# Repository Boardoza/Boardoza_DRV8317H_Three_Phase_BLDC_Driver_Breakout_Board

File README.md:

# Boardoza DRV8317H Three-Phase BLDC Motor Driver Breakout Board

The **Boardoza DRV8317H Breakout Board** is a high-performance, integrated **three-phase BLDC motor driver** designed for compact and efficient motor control applications. Based on the **Texas Instruments DRV8317H**, this device integrates three half-bridges with low R<sub>DS(ON)</sub> MOSFETs, programmable current sensing, and advanced protection mechanisms into a single solution.

Supporting supply voltages up to **24V (absolute maximum)** and delivering up to **5A peak output current**, the DRV8317H is ideal for robotics, steward and gimbal systems, drones, industrial automation, pumps, and smart motorized systems. With flexible control options such as **6x PWM mode and 3x PWM mode**, this board allows both simple and advanced motor control implementations.

## [Click here to purchase!](https://www.ozdisan.com/ureticiler/boardoza)

| Front Side | Back Side |
|:---:|:---:|
|  |  |

---

## Key Features

- **Integrated Three-Phase Driver:** Drives BLDC and PMSM motors with a compact all-in-one solution.
- **Up to 5A Peak Output Current:** Suitable for medium-power motor applications.
- **Flexible Control Options:** Supports **6x PWM** and **3x PWM**.
- **High PWM Frequency Support:** Operates with PWM frequencies up to **200 kHz**.
- **Integrated Current Sensing:** No external shunt resistor required.
- **Programmable Slew Rate:** Helps reduce EMI and optimize switching performance.
- **Comprehensive Protection Features:** Includes UVLO, OVP, CPUV, OCP, OTW, and OTS protections.
- **Shoot-Through Protection:** Integrated hardware-level safety for reliable operation.

---

## Technical Specifications

**Model:** DRV8317H  
**Manufacturer:** Boardoza  
**Manufacturer IC:** Texas Instruments  
**Driver Type:** Integrated 3-Phase Gate Driver with MOSFETs  
**Functions:** Three-Phase PWM BLDC Motor Driver  
**Input Voltage (VM):** 4.5V – 20V (24V Absolute Maximum)  
**Peak Output Current:** 5A (per phase, peak)  
**Control Interfaces:** 6x PWM / 3x PWM    
**Maximum PWM Frequency:** 200 kHz  
**RDS(ON) (HS + LS):** 130 mΩ (typical at 25°C)  
**Current Sensing:** Integrated (Programmable Gain)  
**Protection Features:**  
- UVLO (Undervoltage Lockout)  
- OVP (Overvoltage Protection)  
- CPUV (Charge Pump Undervoltage)  
- OCP (Overcurrent Protection)  
- OTW (Overtemperature Warning)  
- OTS (Overtemperature Shutdown)  

**Operating Temperature:** -40°C to +125°C  
**Board Dimensions:** 60mm x 80mm  

---

## Board Pinout / User Guide

>Pin functions are multiplexed and may vary depending on selected control mode (6x PWM, 3x PWM).  
For detailed pin descriptions, alternate-function mappings, electrical characteristics, and application examples, please refer to the official Board User Guide:
[DRV8317H User Guide.pdf](./assets/DRV8317H%20User%20Guide.pdf)

---

## Board Dimensions

---

## Step Files

[Boardoza DRV8317H.step](./assets/DRV8317%20Step.step)

---

## Datasheet

[DRV8317H Datasheet.pdf](./assets/DRV8317%20Datasheet.pdf)

---

## Version History

- v1.0.0 - Initial Release

---

## Support

- If you have any questions or need support, please contact **support@boardoza.com**

---

## **License**

This repository contains both hardware and software components:

### **Hardware Design**

[![CC BY-SA 4.0][cc-by-sa-shield]][cc-by-sa]

All hardware design files are licensed under [Creative Commons Attribution-ShareAlike 4.0 International License][cc-by-sa].

[cc-by-sa]: http://creativecommons.org/licenses/by-sa/4.0/
[cc-by-sa-shield]: https://img.shields.io/badge/License-CC%20BY--SA%204.0-lightgrey.svg

### **Software/Firmware**

[![BSD-3-Clause][bsd-shield]][bsd]

All software and firmware are licensed under [BSD 3-Clause License][bsd].

[bsd]: https://opensource.org/licenses/BSD-3-Clause
[bsd-shield]: https://img.shields.io/badge/License-BSD%203--Clause-blue.svg

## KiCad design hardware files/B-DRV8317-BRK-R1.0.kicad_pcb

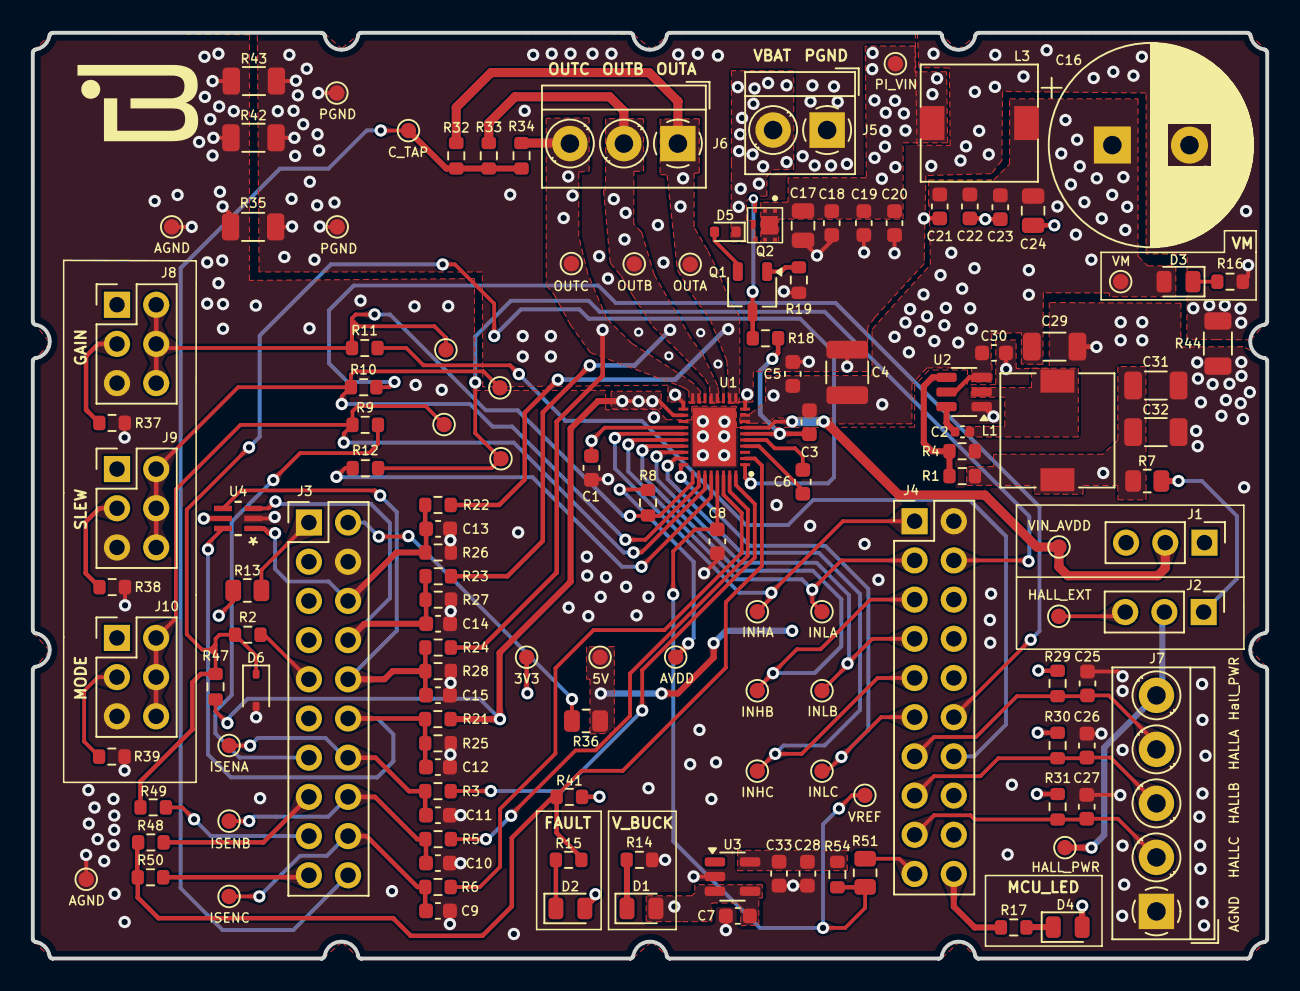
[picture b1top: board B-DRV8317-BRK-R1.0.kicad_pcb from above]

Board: 4 copper layers, 80.0 x 60.0 mm, 135 parts (0 on the bottom side), 71 nets.

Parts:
C1: 4.7uF; C_0603_1608Metric
C2: 0,1uF; C_0402_1005Metric
C3, C28: 1uF; C_0603_1608Metric
C4: 10uF; C_1210_3225Metric
C5, C6, C7, C8, C12, C13, C14, C15, C18, C23, C30, C33: 100nF; C_0603_1608Metric
C9, C10, C11: 22pF; C_0603_1608Metric
C16: 330uF; CP_Radial_D13.0mm_P5.00mm
C17, C24: 1uF; C_0805_2012Metric
C19, C22: 10nF; C_0603_1608Metric
C20, C21, C25, C26, C27: 1nF; C_0603_1608Metric
C29: 2,2uF; C_1206_3216Metric
C31, C32: 22uF; C_1206_3216Metric
D1, D3: GREEN; LED_0805_2012Metric
D2: YELLOW; LED_0805_2012Metric
D4: ORANGE; LED_0805_2012Metric
D5: CDSU101A; D_SOD-523
D6: SZMM3Z3V3ST1G; D_SOD-323
J1, J2: Conn_01x03; PinHeader_1x03_P2.54mm_Vertical
J3, J4: Conn_02x10_Odd_Even; PinHeader_2x10_P2.54mm_Vertical
J5: Conn_01x02; TerminalBlock_MetzConnect_Type059_RT06302HBWC_1x02_P3.50mm_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
J6: Conn_01x03; TerminalBlock_MetzConnect_Type059_RT06303HBWC_1x03_P3.50mm_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
J7: Conn_01x05; TerminalBlock_MetzConnect_Type059_RT06305HBWC_1x05_P3.50mm_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
J8, J9, J10: Conn_02x03_Odd_Even; PinHeader_2x03_P2.54mm_Vertical
L1: SRI0704-100M; L_7.3x7.3_H4.5
L3: 1uH; L_Wuerth_WE-PD-Typ-7345
Q1: FMMT620TA; TSOT-23
Q2: BUK9D23-40EX; TRANS_BUK9D23-40EX
R1, R32, R33, R34: 100k; R_0603_1608Metric
R2, R9, R10, R11, R12, R48, R49, R50, R54: 0; R_0603_1608Metric
R3, R5, R6, R14, R15, R17: 330R; R_0603_1608Metric
R4: 22.1k; R_0603_1608Metric
R7, R13, R36, R51: 0; R_0805_2012Metric
R8, R41: 5.1k; R_0603_1608Metric
R16: 4.70k; R_0603_1608Metric
R18, R19, R29, R30, R31, R47: 10k; R_0603_1608Metric
R21, R22, R23, R24: 42.2k; R_0603_1608Metric
R25, R26, R27, R28: 6.04k; R_0603_1608Metric
R35, R42, R43, R44: 0; R_1206_3216Metric
R37, R38, R39: 47k; R_0603_1608Metric
TP1: OUTA; TestPoint_Pad_D1.0mm
TP2: OUTB; TestPoint_Pad_D1.0mm
TP3: OUTC; TestPoint_Pad_D1.0mm
TP4: VIN_AVDD; TestPoint_Pad_D1.0mm
TP5: PI_VIN; TestPoint_Pad_D1.0mm
TP6: VREF; TestPoint_Pad_D1.0mm
TP7: ISENC; TestPoint_Pad_D1.0mm
TP8: ISENB; TestPoint_Pad_D1.0mm
TP9: ISENA; TestPoint_Pad_D1.0mm
TP10: VM; TestPoint_Pad_D1.0mm
TP11, TP16: GNDA; TestPoint_Pad_D1.0mm
TP12, TP17: GNDP; TestPoint_Pad_D1.0mm
TP14: HALL_EXT; TestPoint_Pad_D1.0mm
TP15: C_TAP; TestPoint_Pad_D1.0mm
TP18: AVDD; TestPoint_Pad_D1.0mm
TP19: 3V3; TestPoint_Pad_D1.0mm
TP20: INHA; TestPoint_Pad_D1.0mm
TP21: INLA; TestPoint_Pad_D1.0mm
TP22: SCLK; TestPoint_Pad_D1.0mm
TP23: INHB; TestPoint_Pad_D1.0mm
TP24: SDI; TestPoint_Pad_D1.0mm
TP25: INLB; TestPoint_Pad_D1.0mm
TP26: SDO; TestPoint_Pad_D1.0mm
TP27: INHC; TestPoint_Pad_D1.0mm
TP28: nSCS; TestPoint_Pad_D1.0mm
TP29: INLC; TestPoint_Pad_D1.0mm
TP30: +5V; TestPoint_Pad_D1.0mm
TP31: HALL_PWR; TestPoint_Pad_D1.0mm
U1: DRV8317HREER; QFN40P400X500X80-37N-D
U2: LMR51420YFDDCR; SOT-23-6
U3: REF4132B33DBVRQ1; SOT-23-5
U4: TPD4S009DCKR; DCK6

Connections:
3.3_BK: C31.1, C32.1, L1.2, R1.2, R7.2
3V3: C7.2, D1.2 (A), D2.2 (A), D4.2 (A), J2.1, R7.1, R13.1, TP19.1, U3.3 (EN), U3.4 (VIN)
+5V: J1.1, R36.2, TP30.1
/CSAREF: C8.2, R51.1, R54.1, TP6.1, U1.33 (CSAREF)
/C_TAP: J3.20, R32.1, R33.1, R34.1, TP15.1
/HALLA: C25.1, J4.13, J7.4, R29.1
/HALLB: C26.1, J4.15, J7.3, R30.1
/HALLC: C27.1, J4.17, J7.2, R31.1
/INHA: J4.1, TP20.1, U1.23 (INHA)
/INHB: J4.5, TP23.1, U1.25 (INHB)
/INHC: J4.9, TP27.1, U1.27 (INHC)
/INLA: J4.3, TP21.1, U1.24 (INLA)
/INLB: J4.7, TP25.1, U1.26 (INLB)
/INLC: J4.11, TP29.1, U1.28 (INLC)
/ISENA: C11.2, J3.14, R3.2, TP9.1
/ISENB: C10.2, J3.16, R5.2, TP8.1
/ISENC: C9.2, J3.18, R6.2, TP7.1
/MCU_LED: J4.20, R17.1
/OUTA: J6.1, R22.2, R32.2, TP1.1, U1.11 (OUTA_1), U1.12 (OUTA_2)
/OUTB: J6.2, R23.2, R33.2, TP2.1, U1.14 (OUTB_1), U1.15 (OUTB_2)
/OUTC: J6.3, R24.2, R34.2, TP3.1, U1.17 (OUTC_1), U1.18 (OUTC_2)
/SCLK: J3.13, R9.1
/SCLK/MODE: J10.2, J10.4, J10.6, R9.2, TP22.1, U1.31 (SCLK)
/SDI: J4.12, R10.1
/SDI/SLEW: J9.2, J9.4, J9.6, R10.2, TP24.1, U1.30 (SDI)
/SDO: J4.14, R11.1
/SDO/GAIN: J8.2, J8.4, J8.6, R8.1, R11.2, TP26.1, U1.29 (SDO)
/SOA: R3.1, U1.36 (SOA)
/SOB: R5.1, U1.35 (SOB)
/SOC: R6.1, U1.34 (SOC)
/VSENA: C13.1, J3.6, R22.1, R26.2, U4.1 (D1+)
/VSENB: C14.1, J3.8, R23.1, R27.2, U4.3 (D2+)
/VSENC: C15.1, J3.10, R24.1, R28.2, U4.4 (D2-)
/VSENVM: C12.1, J3.12, R21.1, R25.2, U4.6 (D1-)
/nFAULT: R15.1, R41.1, R48.1, R50.1, U1.2 (NFAULT)
/nSCS: J4.4, R12.1, TP28.1
/nSCS/NC: R12.2, U1.32 (nSCS)
AGND: C1.2, C7.1, C8.1, C9.1, C10.1, C11.1, C12.2, C13.2, C14.2, C15.2, C25.2, C26.2, C27.2, C28.1, C29.1, C30.1, C31.2, C32.2, C33.1, D6.2 (A), J3.4, J4.2, J7.1, J8.5, J9.5, J10.5, R4.1, R14.1, R25.1, R26.1, R27.1, R28.1, R35.2, R37.1, R38.1, R39.1, R42.2, R43.2, R44.2, TP11.1, TP16.1, U1.21 (AGND), U1.37 (GND), U2.1 (GND), U3.2 (GND), U4.2 (GND)
AVDD: C1.1, J8.1, J9.1, J10.1, R8.2, R29.2, R30.2, R31.2, R41.2, TP18.1, U1.22 (AVDD), U4.5 (VCC)
HALL_PWR: J2.2, J7.5, TP31.1
unnamed: C17.1, C18.1, C19.1, C20.1, L3.1, Q2.1, Q2.2, Q2.5, Q2.6, Q2.7, TP5.1
unnamed: D1.1 (K), R14.2
unnamed: D2.1 (K), R15.2
unnamed: D3.1 (K), R16.2
unnamed: D4.1 (K), R17.2
unnamed: D5.2 (A), Q1.2 (E)
unnamed: J2.3, TP14.1
unnamed: J3.1, R13.2
unnamed: J3.2, R36.1
unnamed: J3.9, R2.2
unnamed: J3.15, R48.2
unnamed: J3.17, R49.2
unnamed: J3.19, R50.2
unnamed: J4.19, R51.2
unnamed: J8.3, R37.2
unnamed: J9.3, R38.2
unnamed: J10.3, R39.2
unnamed: Q1.1 (B), R19.2
unnamed: Q1.3 (C), Q2.3, R18.2
unnamed: C6.2, U1.5 (CPH)
unnamed: C6.1, U1.4 (CPL)
unnamed: C2.2, U2.6 (CB)
unnamed: R1.1, R4.2, U2.4 (FB)
unnamed: C2.1, L1.1, U2.2 (SW)
unnamed: C28.2, C33.2, R54.2, U3.5 (VREF)
PGND: C4.2, C5.2, C16.2, C17.2, C18.2, C19.2, C20.2, C21.2, C22.2, C23.2, C24.2, J5.1, R16.1, R19.1, R35.1, R42.1, R43.1, R44.1, TP12.1, TP17.1, U1.10 (PGND_1), U1.13 (PGND_2), U1.16 (PGND_3), U1.19 (PGND_4)
VBAT: D5.1 (K), J5.2, Q2.4, Q2.8
VCP: C3.2, R18.1, U1.6 (CP)
VIN_AVDD: J1.2, TP4.1, U1.7 (VIN_AVDD)
VM: C3.1, C4.1, C5.1, C16.1, C21.1, C22.1, C23.1, C24.1, C29.2, C30.2, D3.2 (A), J1.3, L3.2, R21.2, R47.2, TP10.1, U1.8 (VM_1), U1.9 (VM_2), U1.20 (VM_3), U2.3 (VIN), U2.5 (EN)
nSLEEP: D6.1 (K), R2.1, R47.1, R49.1, U1.1 (~SLEEP)

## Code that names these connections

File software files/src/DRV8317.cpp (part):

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 * @param pwmPinA PWM pin A number.
 * @param pwmPinB PWM pin B number.
 * @param pwmPinC PWM pin C number.
 * @param nSleepPin nSleep pin number.
 * @param hallA Hall sensor A pin number.
 * @param hallB Hall sensor B pin number.
 * @param hallC Hall sensor C pin number.
 */
DRV8317::DRV8317(uint8_t in1LPin, uint8_t in2LPin, uint8_t in3LPin, uint8_t pwmPinA, uint8_t pwmPinB, uint8_t pwmPinC, uint8_t nSleepPin, uint8_t hallA, uint8_t hallB, uint8_t hallC) {
    _in1LPin = in1LPin;
    _in2LPin = in2LPin;
    _in3LPin = in3LPin;
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    pinMode(_pwmPinB, OUTPUT);
    pinMode(_pwmPinC, OUTPUT);
    pinMode(_nSleepPin, OUTPUT);
    pinMode(_hallA, INPUT);
    pinMode(_hallB, INPUT);
    pinMode(_hallC, INPUT);
    analogWriteFrequency(100000);
    enable();
    //disable();
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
